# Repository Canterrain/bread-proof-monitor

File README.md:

# Bread Proof Monitor

A dough rise monitor that helps you know when it's time to fold, shape, or bake.

Place the sensor over your dough, choose a bread profile, and follow the rise from your phone. The monitor keeps track of progress, reminds you about folds, and can send a notification when your dough reaches its target.

Built for an ESP32 with a distance sensor and a temperature and humidity sensor. The dashboard runs on the monitor itself and opens in a browser on your home network.

## ✨ Features

- Live dough rise, elapsed time, temperature, and humidity
- Profiles for everyday breads, sourdough, pizza, rolls, and more
- Links to the recipes the profiles are based on
- Fold reminders for recipes with handling steps
- Separate bulk and final proof targets
- Optional phone alerts through ntfy: fold reminders, Ready to Shape, and Ready to Bake
- Pause and resume while you handle the dough
- Feedback that adjusts future targets for your recipe and setup
- Wi-Fi setup from your phone, with no credentials to put in the code
- Installation over USB from your browser

The targets are starting points. Flour, hydration, temperature, and starter or yeast strength all affect a proof. Use the reading alongside how your dough looks and feels.

## 🛠 Hardware

This project is designed around these specific boards and sensor modules:

- [ELEGOO 3PCS ESP-32 Dev Boards](https://amzn.to/46aN2Hq) (affiliate; one board needed)
- [HiLetgo SHT31-D Temperature and Humidity Sensor](https://amzn.to/4xLTMYm) (affiliate)
- [VL53L0X Time-of-Flight Ranging Sensor](https://amzn.to/4xEbyg1) (affiliate)

You'll also need:

- A USB data cable and USB power supply
- A container, and something that holds the distance sensor above the dough

That mount can be as simple as it sounds: the working prototype this project was developed on is just jumper-wired breakouts hot-glued or taped into a lid, on a stand of legs for containers that need one. No PCB is required to build or use this project.

The browser installer is for the original ESP32 chip. ESP32-C3, S3, and P4 boards need different firmware.

### Wiring

Both sensors share the same I²C bus:

| ESP32 | VL53L0X breakout | SHT31 breakout |
| --- | --- | --- |
| 3V3 | VIN / VCC | VIN / VCC |
| GND | GND | GND |
| **GPIO22** | **SDA** | **SDA** |
| **GPIO21** | **SCL** | **SCL** |

Use the pin labels on your particular breakout. This project's SDA and SCL assignments differ from the usual ESP32 defaults.

Mount the distance sensor securely above the dough with room for the tallest expected rise. Keep the sensor as close as that clearance allows. A long distance above a thin layer of dough makes small measurement changes look like much larger changes in rise.

### Optional: Rev A Carrier PCB

If you'd rather not hand-wire and hot-glue sensors into a lid, a custom carrier PCB is available as a drop-in alternative to the wiring table above — plug-in sockets for the ELEGOO EL-SM-012, ALAMSCN VL53L0X-V2, and HiLetgo GY-SHT31-D modules replace the loose wiring entirely. It's entirely optional; the software doesn't know or care which mounting approach you used. Its [KiCad files and manufacturing package](hardware/kicad/rev-a/README.md) are included — see the [hardware guide](guides/hardware.md) for ordering and assembly steps. The lid and enclosure design is still in progress, so even with the PCB you'll still need your own way to mount it.

## 🚀 Quick Start

### Install the software

Use Chrome, Edge, or a Firefox version with Web Serial support on a desktop or laptop. Safari and mobile browsers aren't supported by this installer.

1. Plug the ESP32 into your computer with a USB **data** cable.
2. Open the **[Bread Proof Monitor installer](https://canterrain.github.io/bread-proof-monitor/)**.
3. Click **Connect**, choose your board, and select **Install**.
4. For a first installation, select **Erase device**. Wait for installation to finish and the board to restart.

You don't need Arduino IDE to use the browser installer. If you'd rather build it yourself, see the [build guide](guides/development.md).

### Connect to Wi-Fi

1. Open your phone or computer's **Wi-Fi settings** and join **ProofMonitor-Setup**. The password is **sourdough**.
2. Open [http://192.168.4.1](http://192.168.4.1).
3. Choose your home Wi-Fi network and enter its password.
4. If you want phone alerts, copy the generated ntfy topic and subscribe to it in the ntfy app.
5. Save, wait for the monitor to restart, and reconnect your phone or computer to your home network.
6. Open **[http://proofmonitor.local](http://proofmonitor.local)**.

If that address doesn't open, use the monitor's IP address from your router's connected-device list.

## Using the Monitor

Choose a profile and apply its target. With the empty container and lid in their normal positions, press **Set Empty Setup**. Add the dough, let the lid settle, then press **Set Starting Dough Height**.

The dashboard shows the rise, time, and next step. When a fold is due:

1. Press **Pause Monitoring** before lifting the lid.
2. Fold the dough and put the lid back.
3. Press **Resume Monitoring**, allow the reading to settle, then press **Complete Step**.

When the target is reached, check the dough before pressing **Finish Proof**. For profiles with a monitored final proof, the monitor then prepares the Final stage. Most profiles ask you to calibrate the empty final-proof setup again before setting a new starting height.

Some recipes finish with refrigerated rests or stages that aren't useful to track by height. The monitor tells you when to continue with the linked recipe.

The [usage guide](guides/usage.md) covers calibration, pauses, re-baselining, target confirmation, and starting another batch.

## 🔔 Phone Alerts

Alerts use [ntfy](https://ntfy.sh/). Subscribe to the topic shown during setup to get fold reminders and Ready to Shape or Ready to Bake notifications.

The monitor generates a random topic for you. Treat that topic like a private link: anyone who knows it can subscribe or send messages to it. The dashboard works locally; delivering phone alerts requires internet access.

## Learning Your Dough

After each stage, rate the dough **Underproofed**, **Just Right**, or **Overproofed**, based on what you saw when that stage finished.

Two matching underproofed or overproofed ratings move that recipe and stage's suggested target by five percentage points. Adjustments stay within 25 points of the original suggestion. A Just Right rating clears the streak and keeps the adjustment.

Your feedback is saved on the device. Learned targets are used when you select a profile and when the monitor prepares Final proof. A proof keeps the target you've already applied. **Reset Learned Targets** clears the stored adjustments.

## Updating

Reconnect the ESP32 to your computer and use the same browser installer. For an update from this project's existing 4 MB / Huge APP layout, leave **Erase device** unchecked to retain saved settings. Erasing clears Wi-Fi, calibration, progress, the ntfy topic, and learned targets; repeat first-time setup afterward.

Update between proofs. Wireless updates aren't included.

## Development

The firmware uses Arduino for ESP32. See the [development guide](guides/development.md) for dependencies, local builds, and how to prepare a new browser-installable version.

| Path | What's there |
| --- | --- |
| `bread_proof_monitor.ino` | Startup and main loop |
| `app_state.*`, `proof_state.*` | Saved settings, rise calculations, and proof steps |
| `sensor_reader.*` | Distance, temperature, and humidity readings |
| `recipe_presets.*`, `outcome_feedback.*` | Profiles and learned target adjustments |
| `web_dashboard.*`, `web_assets.h` | Dashboard and setup pages |
| `notifications.*`, `wifi_setup.*` | Phone alerts and Wi-Fi |
| `docs/` | GitHub Pages installer and firmware files |
| `guides/` | Usage, development, and publishing instructions |
| `hardware/` | Carrier PCB design and manufacturing files |
| `tools/` | Local build, upload, and firmware packaging tools |

## Related Projects

- [Round Weather Display](https://github.com/Canterrain/round-weather-display), a round clock and weather display for Raspberry Pi or ESP32-P4
- [Weather Display](https://github.com/Canterrain/weather-display), a wider clock and weather display for under a cabinet or on a desk
- [Inky Planner](https://github.com/Canterrain/Inky-Planner), a daily planner for Raspberry Pi and Inky e-paper displays

## 📃 License

This project is licensed under the [Creative Commons Attribution–NonCommercial 4.0 International License](https://creativecommons.org/licenses/by-nc/4.0/). See [LICENSE](LICENSE). Third-party libraries retain their own licenses.

© 2026 Josh Hendrickson

Made by [Josh Hendrickson](https://anoraker.com)

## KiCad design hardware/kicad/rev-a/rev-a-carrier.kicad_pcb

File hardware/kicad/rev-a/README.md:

# Rev A Carrier PCB

Reference documentation for the Bread Proof Monitor carrier PCB: a small board that gives the ESP32 module and both sensor breakouts a rigid, repeatable mount on the underside of a lid, using plug-in sockets instead of loose wiring.

## Status

- Schematic and PCB are complete. ERC: 0 errors, 0 warnings. DRC: 0 errors, 1 accepted cosmetic warning (see [Exclusions](#exclusions)).
- Routed at conventional prototype design rules — 0.25 mm trace, 0.6 mm/0.3 mm via, 0.2 mm clearance. No relaxed tolerances.
- All PCB-affecting mechanical decisions are finalized (VL53L0X optical alignment, SHT31 retention approach — see `mechanical-stackup.md`).
- Gerbers, drill files, and the full manufacturing package are generated and ready to order — see [Manufacturing Package](#manufacturing-package).
- Not yet designed: the lid/enclosure itself. Nothing here depends on it; see `mechanical-stackup.md` for the parametric interface (optical bore, vent pocket, standoff heights) it will need to satisfy.

## Bill of Materials

### Carrier-assembled (populated by the PCB assembly house)

| Ref | Part | Qty | Represents |
| --- | --- | ---: | --- |
| J1, J2 | Samtec `SSW-115-01-T-S` (1×15, 2.54 mm, THT) | 2 | Sockets the ELEGOO EL-SM-012 ESP32 module plugs into |
| J3 | Samtec `SSW-106-01-T-S` (1×6, 2.54 mm, THT) | 1 | Socket for the VL53L0X breakout |
| J4 | Samtec `SSW-104-01-T-S` (1×4, 2.54 mm, THT) | 1 | Socket for the SHT31 breakout |

J1 and J2 are the same physical part in two positions (a BOM grouped by MPN reports them as one line, qty 2). All four sockets are the same Samtec SSW family: 2.54 mm pitch, single-row, through-hole, lead-free (`-S`).

`U1` is a silkscreen/mechanical reference only for the ESP32 module's outline — zero pads, `in_bom=no`, `dnp=yes`. It never appears in a BOM export.

### User-installed (not part of the PCB order)

| Plugs into | Part | Amazon ASIN |
| --- | --- | --- |
| J1 + J2 | ELEGOO EL-SM-012 (ESP32 dev module) | B0D8T53CQ5 |
| J3 | ALAMSCN black VL53L0X-V2 breakout | B0DGL2P6XC |
| J4 | HiLetgo GY-SHT31-D breakout | B07ZSZW92J |

The EL-SM-012 plugs directly into J1/J2 using its own existing pin rows — nothing to solder. The VL53L0X-V2 and SHT31 breakouts (J3, J4) ship with loose 2.54 mm male header strips that need to be soldered onto the breakout before it plugs into the carrier.

## Pinout

### EL-SM-012 (ESP32 module) pin map

Verified directly against the [EL-SM-012 manual's pinout diagram](https://manuals.plus/asin/B0D8T53CQ5) (Section 5, Figure 5.1). Only the four pads below carry nets; the rest of the header exists for mechanical support only.

| Pad | Function | Pad | Function |
| ---: | --- | ---: | --- |
| 1 | VIN (5V) | 16 | **3V3** |
| 2 | **GND** | 17 | **GND** |
| 3 | GPIO13 | 18 | GPIO15 |
| 4 | GPIO12 | 19 | GPIO2 |
| 5 | GPIO14 | 20 | GPIO4 |
| 6 | GPIO27 | 21 | GPIO16 |
| 7 | GPIO26 | 22 | GPIO17 |
| 8 | GPIO25 | 23 | GPIO5 |
| 9 | GPIO33 | 24 | GPIO18 |
| 10 | GPIO32 | 25 | GPIO19 |
| 11 | GPIO35 | 26 | **GPIO21 (SCL)** |
| 12 | GPIO34 | 27 | GPIO3 (RX0) |
| 13 | GPIO39 (VN) | 28 | GPIO1 (TX0) |
| 14 | GPIO36 (VP) | 29 | **GPIO22 (SDA)** |
| 15 | EN | 30 | GPIO23 |

**Warning:** pad 1 is VIN — raw 5V from USB — not 3V3. Only pads 16 (3V3) and 17 (GND) feed the sensor rail; both sensors are 3.3V-only parts. All four connected pads (3V3, GND, SDA, SCL) sit on the same header column (16-30); the other column (1-15) carries no nets on this board.

The GPIO22 → SDA / GPIO21 → SCL assignment is a firmware convention, not a hardware requirement — it matches the wiring already used by the ESP32 sketch itself. The EL-SM-012's own silkscreen shows a different default for the Wire library; this board's net assignment intentionally overrides that default.

### Connector and mounting-hole reference

`LID_ORIGIN` (0, 0) is the geometric center of the dough/container reference plane, and doubles as `TOF_ORIGIN` — the VL53L0X's optical axis is placed exactly there by construction (J3 is rotated 180° so its optical center, not its mounting-hole midpoint, lands on the datum). Coordinates below are relative to `LID_ORIGIN`; +X toward the antenna notch, +Y toward the ESP32 header.

| Feature | Coordinate (mm) | Notes |
| --- | ---: | --- |
| J3 (VL53L0X) mounting holes | (-10, -2.2) / (+10, -2.2) | Hole-midpoint sits at (0, -2.2), not `LID_ORIGIN` — the sensor's actual optical axis is what's aligned to the datum instead |
| J4 (SHT31) footprint origin (pin 1 / VIN) | (0, -29) | Not a mechanical datum. Retention is a lid/enclosure pocket-clip, not a PCB feature |
| U1 (ESP32 module outline) footprint origin | (0, +27) | Mechanical reference only, not a BOM item |
| J1 / J2 (ESP32 carrier sockets) | (-17.78, +14.18) / (-17.78, +39.82) | Local pin 1 of each |
| MH1 / MH2 / MH3 (carrier mounting holes) | (+40, 0) / (-40, 0) / (0, -45) | 3.2 mm NPTH, M3 clearance, provisional pending host hardware |

## Board Outline

A circle with a USB-C access notch and an antenna overhang notch, rather than a plain circle or a custom polygon — a plain circle large enough to clear the ESP32 module would need to be bigger still and wouldn't give cable/antenna clearance on its own.

- **Base circle:** radius 52 mm, centered on `LID_ORIGIN`. Overall envelope: X/Y from -52.0 to +52.0 mm (~104 × 104 mm).
- **USB-C notch:** board material stops at X = -25 mm, open from there to the edge across Y = 17-37 mm. The EL-SM-012's USB-C connector sits just past this cut, fully in open air.
- **Antenna notch:** board material stops at X = +21 mm, open across the same Y range, 3.22 mm past J1/J2's last pin — giving the WROOM antenna genuine physical overhang rather than relying only on a copper keepout.
- The board's lower size bound is the EL-SM-012 module's own footprint (51.74 × 29.00 mm); its farthest structurally-needed corner sits 50.3 mm from `LID_ORIGIN`, leaving a 1.7 mm margin at the 52 mm radius.

## Antenna Clearance

- `ESP32_ANTENNA_KEEP_OUT`, on both F.Cu and B.Cu: X 9-65 mm, Y 15-39 mm (56 × 24 mm) — no tracks, vias, or zone fills permitted inside it.
- Board material itself ends at X = 21 mm (the antenna notch above), so this region has no FR4 at all, not just no copper.
- The SDA trace's closest approach (pad 29, local X = +15.24 mm) jogs into its routing lane above the header row before heading down the board, so it never enters the keepout's Y band.

## Routing

- **Shared trunks, not per-destination lanes.** 3V3, SDA, and SCL each get one trunk from J2, which tees off to J3 and continues to J4 — not a separate trunk per destination. This keeps routing to 3 lanes at conventional design rules.
- **GND has no explicit trace.** J2, J3, and J4's GND pads are through-hole and sit directly inside the filled F.Cu/B.Cu ground pours; three stitching vias tie the two copper layers together away from the signal corridor. Verified directly against KiCad's own connectivity graph (not inferred from geometry) — J2's GND pad and both sensors' GND pads resolve to the same connected copper network.
- All routing lives on B.Cu, with a handful of via hops to F.Cu to resolve a few crossings.
- 15 vias total: 12 signal-routing detour vias (3V3 ×8, SCL ×4, SDA ×0) plus 3 GND stitching vias. Minimum via-to-via spacing: 0.7 mm edge-to-edge.

## Mechanical Clearances

No copper or courtyard overlap anywhere on the board:

- J1 (top, nearest neighbor to J3) to J3 (bottom): 3.93 mm Y gap.
- J3 to J4 (both bottom): 4.60 mm Y gap.

## Exclusions

1. **Silkscreen clipped by the board edge** — U1's own reference outline rectangle on F.SilkS is clipped at the USB-C notch, since the real EL-SM-012 module genuinely overhangs that cutout by design. Cosmetic only; has no fabrication impact.

## Manufacturing Package

`RevA_Manufacturing_2026-08-26/` contains the complete fabrication and assembly output — Gerbers, Excellon drill files with maps and a report, the final assembly BOM, a placement/position file, a fabrication drawing, and `RevA_Gerbers_NextPCB.zip` (Gerbers + drill files pre-zipped for direct upload to NextPCB's quote tool). See that directory's own `README.md` for the full contents list, fabrication notes, and its change history.

## References

- [EL-SM-012 manual and dimensional drawing](https://manuals.plus/asin/B0D8T53CQ5) — pinout diagram in Section 5, Figure 5.1
- [HiLetgo GY-SHT31-D product listing, ASIN B07ZSZW92J](https://www.amazon.com/dp/B07ZSZW92J)
- [ALAMSCN VL53L0X-V2 product listing, ASIN B0DGL2P6XC](https://www.amazon.com/dp/B0DGL2P6XC)

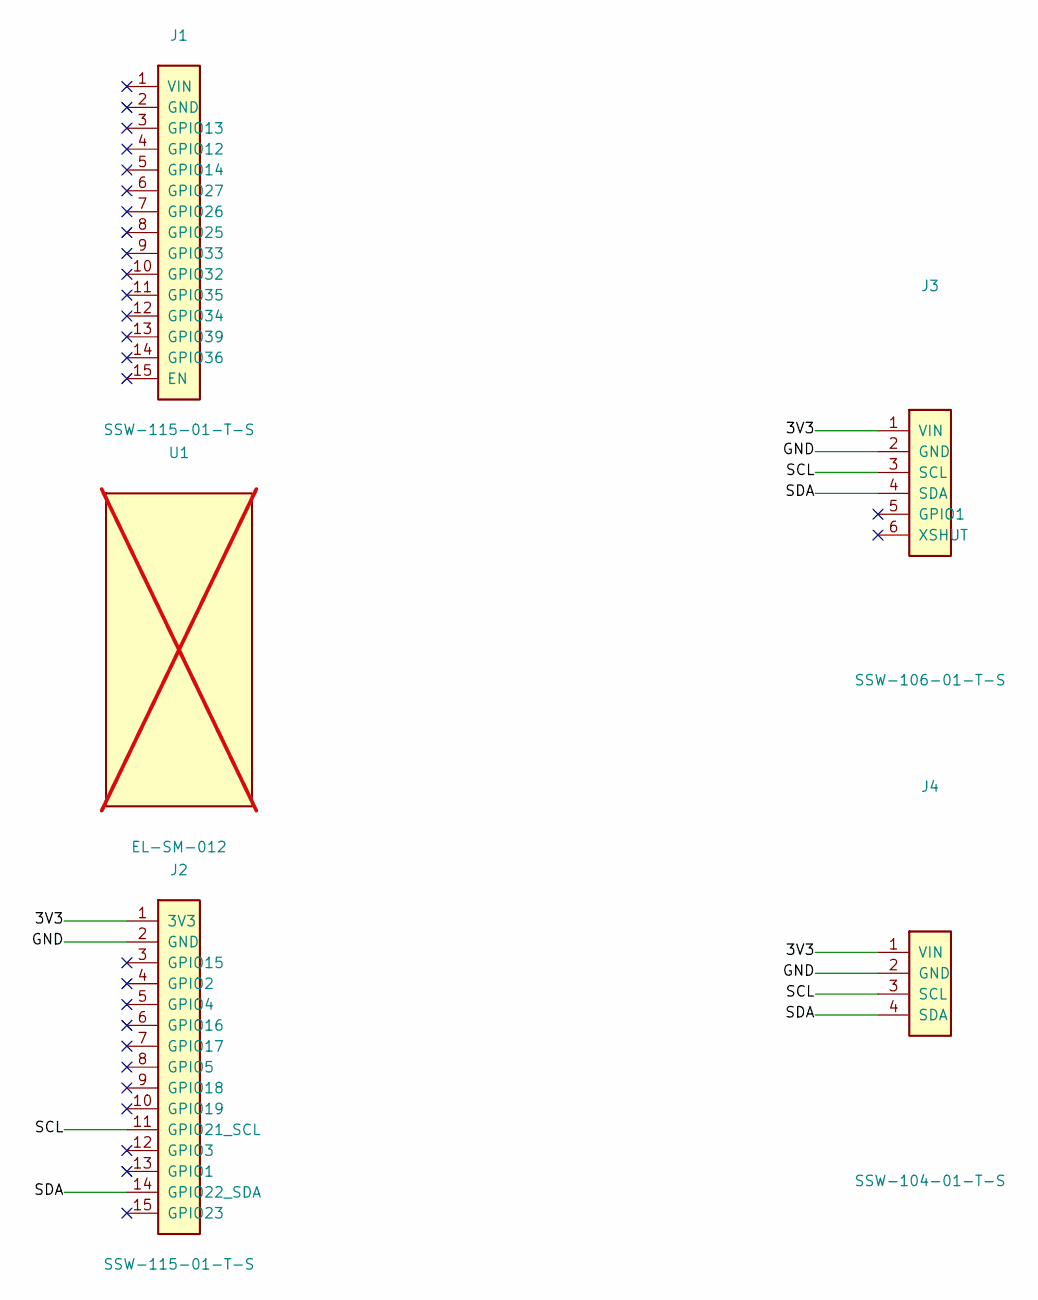
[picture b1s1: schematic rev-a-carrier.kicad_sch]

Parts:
J1, J2: SSW-115-01-T-S; SSW-115-01-T-S_1x15; MPN SSW-115-01-T-S
J3: SSW-106-01-T-S; VL53L0X_V2_1x06_2H_PRELIM; MPN SSW-106-01-T-S
J4: SSW-104-01-T-S; SHT31_GY-SHT31-D_1x04_PRELIM; MPN SSW-104-01-T-S
U1: EL-SM-012; ESP32_EL_SM_012_MODULE_OUTLINE; not fitted

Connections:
3V3: J2.1 (3V3), J3.1 (VIN), J4.1 (VIN)
GND: J2.2 (GND), J3.2 (GND), J4.2 (GND)
SCL: J2.11 (GPIO21_SCL), J3.3 (SCL), J4.3 (SCL)
SDA: J2.14 (GPIO22_SDA), J3.4 (SDA), J4.4 (SDA)

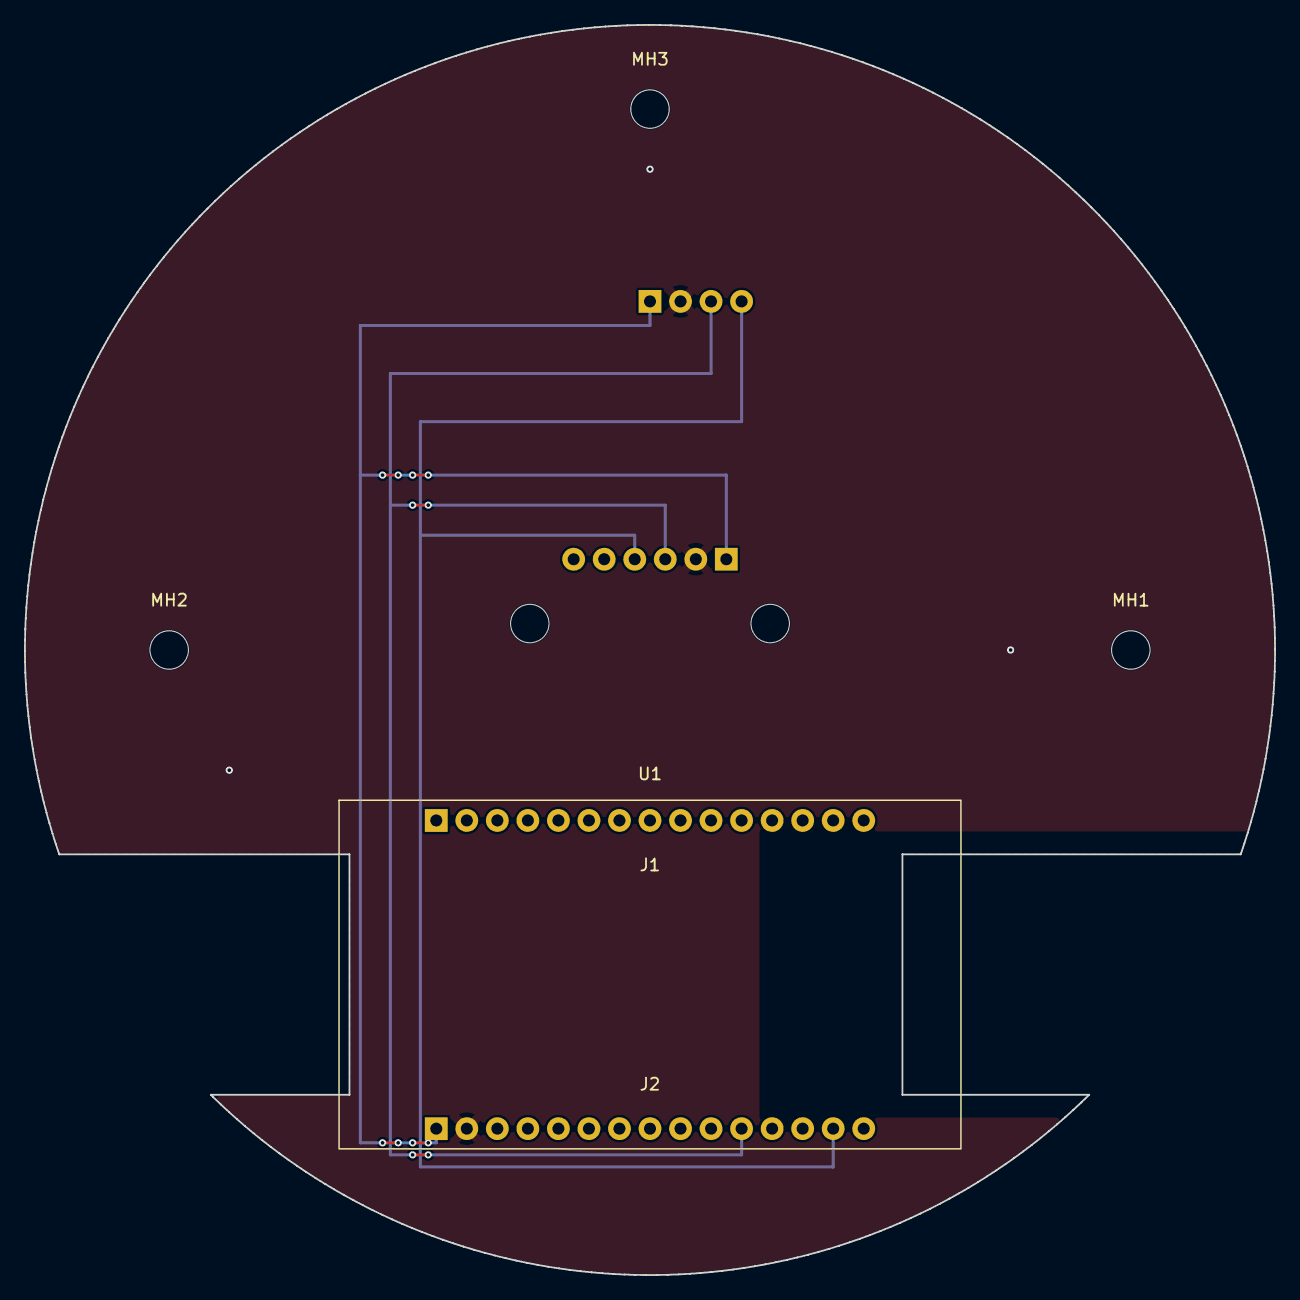
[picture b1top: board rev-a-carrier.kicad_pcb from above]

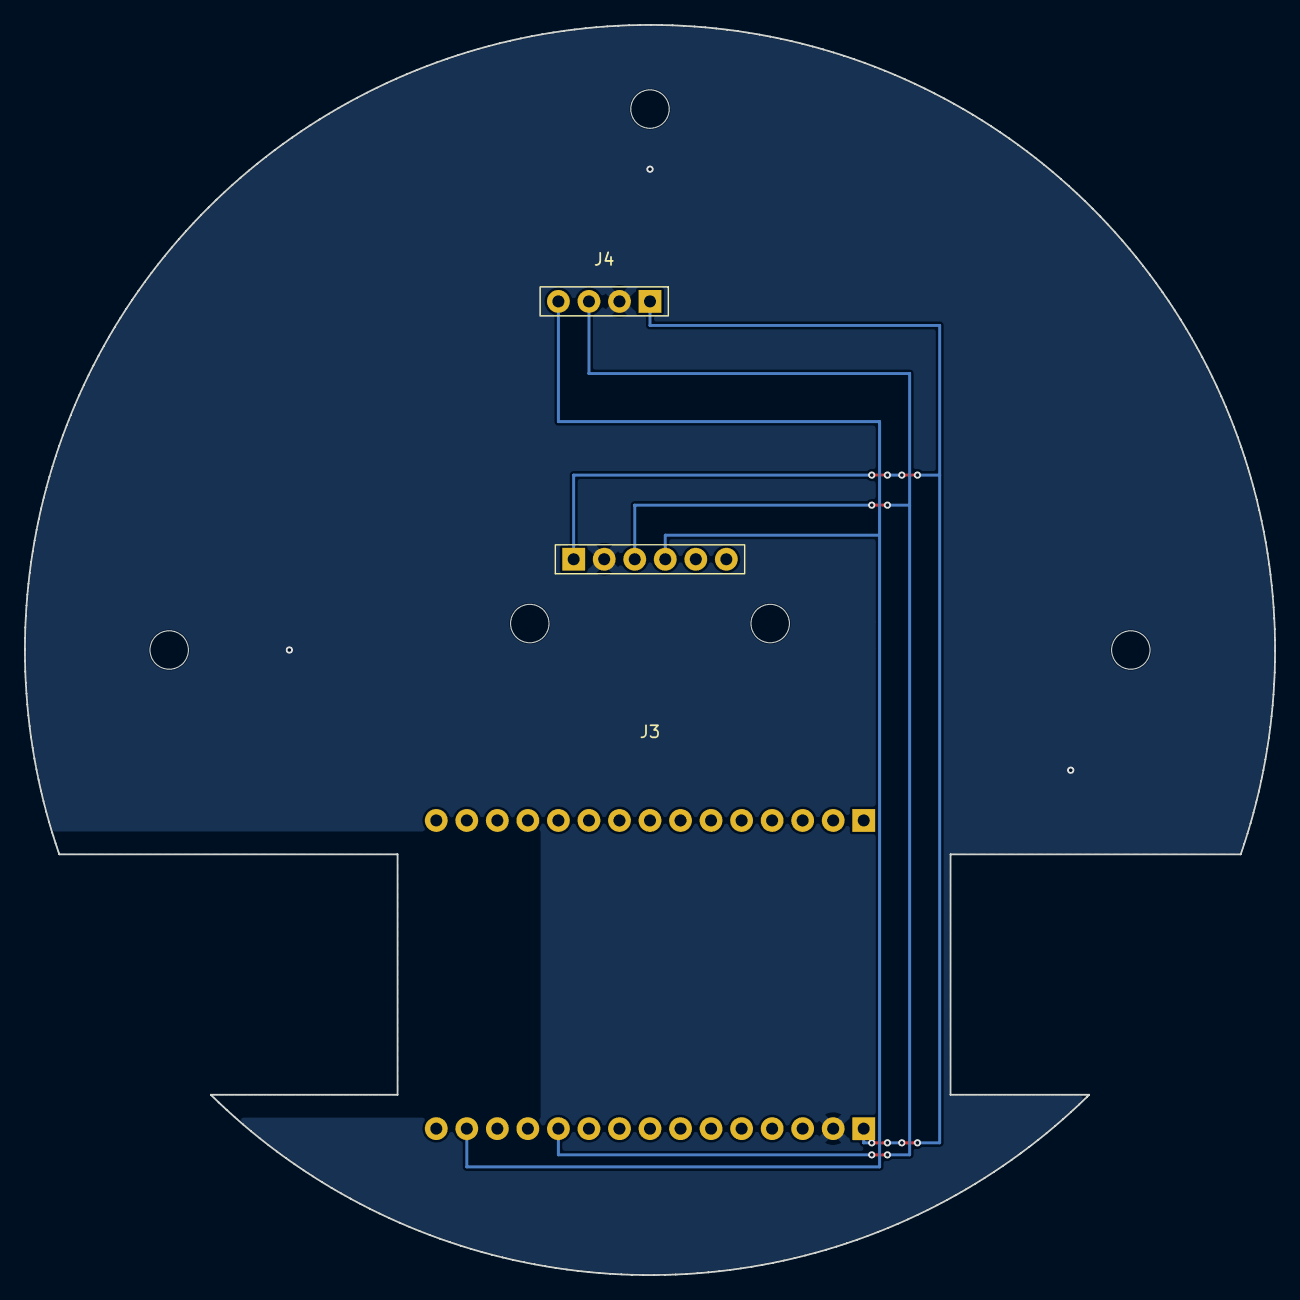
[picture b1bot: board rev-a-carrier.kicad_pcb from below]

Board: 2 copper layers, 104.0 x 104.0 mm, 8 parts (2 on the bottom side), 4 nets.

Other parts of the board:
MH1, MH2, MH3: MountingHole_3.2mm_M3

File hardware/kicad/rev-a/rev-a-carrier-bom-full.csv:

"Refs","Value","Manufacturer","MPN","Footprint","Qty","DNP","ExclBOM"
"J1","SSW-115-01-T-S","Samtec","SSW-115-01-T-S","RevA_Sensors:SSW-115-01-T-S_1x15","1","",""
"J2","SSW-115-01-T-S","Samtec","SSW-115-01-T-S","RevA_Sensors:SSW-115-01-T-S_1x15","1","",""
"J3","SSW-106-01-T-S","Samtec","SSW-106-01-T-S","RevA_Sensors:VL53L0X_V2_1x06_2H_PRELIM","1","",""
"J4","SSW-104-01-T-S","Samtec","SSW-104-01-T-S","RevA_Sensors:SHT31_GY-SHT31-D_1x04_PRELIM","1","",""
